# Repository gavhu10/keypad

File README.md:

# Keypad

This is my first pcb project. It uses an esp32-s3 and was made in KiCad.

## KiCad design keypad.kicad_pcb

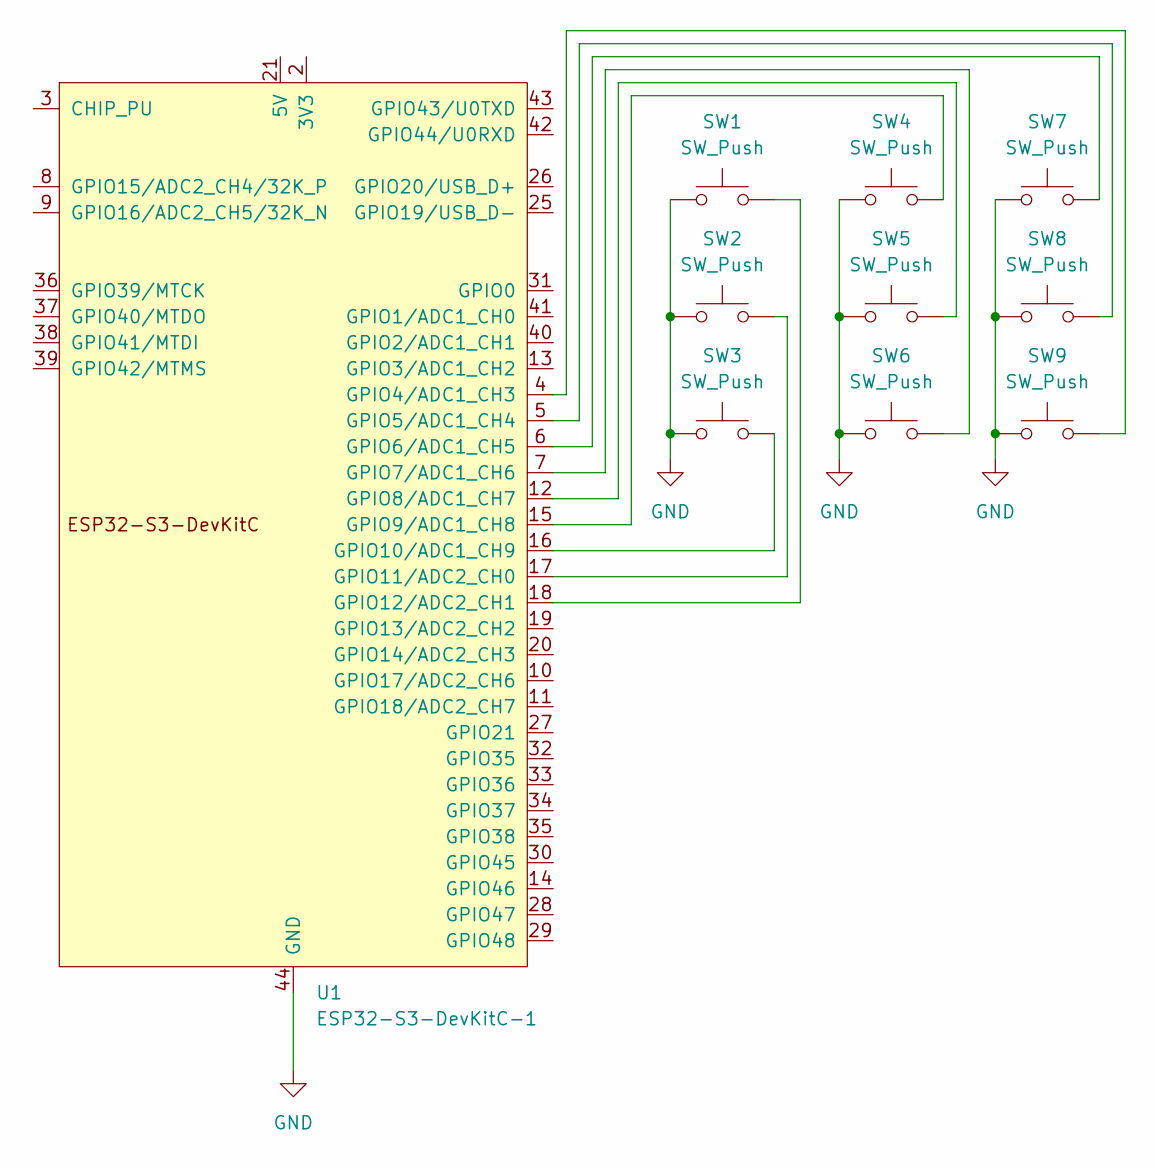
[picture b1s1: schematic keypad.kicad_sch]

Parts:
SW1, SW2, SW3, SW4, SW5, SW6, SW7, SW8, SW9: SW_Push; SW_PUSH-12mm
U1: ESP32-S3-DevKitC-1; ESP32-S3-DevKitC-1-ish

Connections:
GND: SW1.1, SW2.1, SW3.1, SW4.1, SW5.1, SW6.1, SW7.1, SW8.1, SW9.1, U1.22 (GND), U1.23 (GND), U1.24 (GND), U1.44 (GND)
unnamed: U1.1 (3V3), U1.2 (3V3)
unnamed: SW9.2, U1.4 (GPIO4/ADC1_CH3)
unnamed: SW8.2, U1.5 (GPIO5/ADC1_CH4)
unnamed: SW7.2, U1.6 (GPIO6/ADC1_CH5)
unnamed: SW6.2, U1.7 (GPIO7/ADC1_CH6)
unnamed: SW5.2, U1.12 (GPIO8/ADC1_CH7)
unnamed: SW4.2, U1.15 (GPIO9/ADC1_CH8)
unnamed: SW3.2, U1.16 (GPIO10/ADC1_CH9)
unnamed: SW2.2, U1.17 (GPIO11/ADC2_CH0)
unnamed: SW1.2, U1.18 (GPIO12/ADC2_CH1)

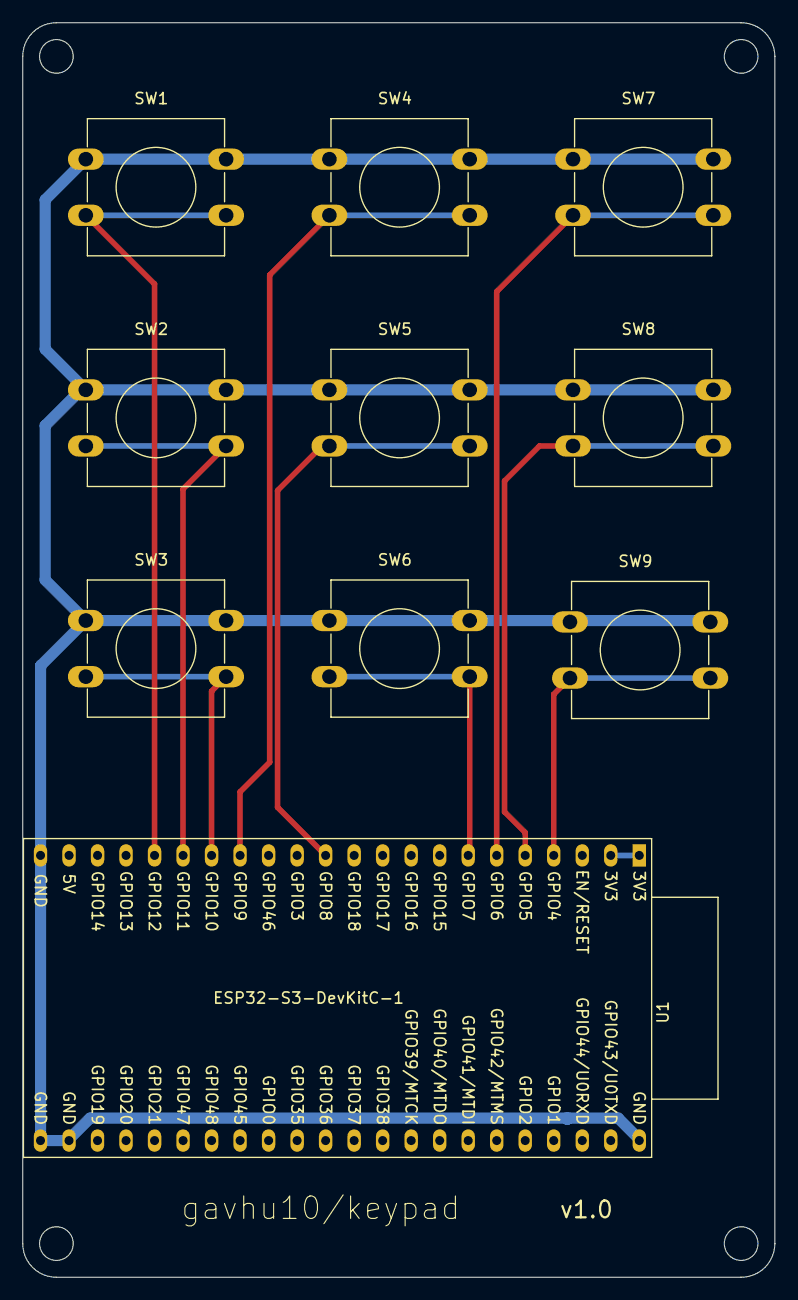
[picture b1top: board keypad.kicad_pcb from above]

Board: 2 copper layers, 67.0 x 111.8 mm, 10 parts (0 on the bottom side), 11 nets.

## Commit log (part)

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2026-05-27 init
2026-05-28 start pbc
2026-05-29 spaced out buttons
2026-05-30 fix board size
2026-05-30 add edge
2026-05-30 move connections
    I moved all the connections so that they make more sense on the pbc.
2026-05-30 fix grounding on schematic
2026-05-30 route board
2026-05-30 add mounting holes
2026-05-30 remove backups
2026-06-02 add some art
2026-06-02 fix drc errors and violations
2026-06-03 reroute board
2026-06-04 prepare for prod
2026-06-14 add pics
